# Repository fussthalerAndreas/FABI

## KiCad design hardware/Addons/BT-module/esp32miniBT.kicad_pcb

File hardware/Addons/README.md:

# FABI Hardware Addons

This folder contains any additional piece of software hardware or gadget to increase the usability of the FABI box.
Since we use a plain Arduino Pro Micro, these addons are fitted on the corresponding and available pin headers.

## BT-module

The BT module is an ESP32 based addon board for the FABI box. It is placed via pin headers (please do not solder directly, as it is likely that the USB port will break some day) on the supply & serial pins.
This folder here contains the KiCAD design files for PCB production.
Please refer to [esp32_mouse_keyboard](https://github.com/asterics/esp32_mouse_keyboard) repository for the corresponding source code.

This design was done in KiCAD __v5.1.6__. Please use a version equal or newer.

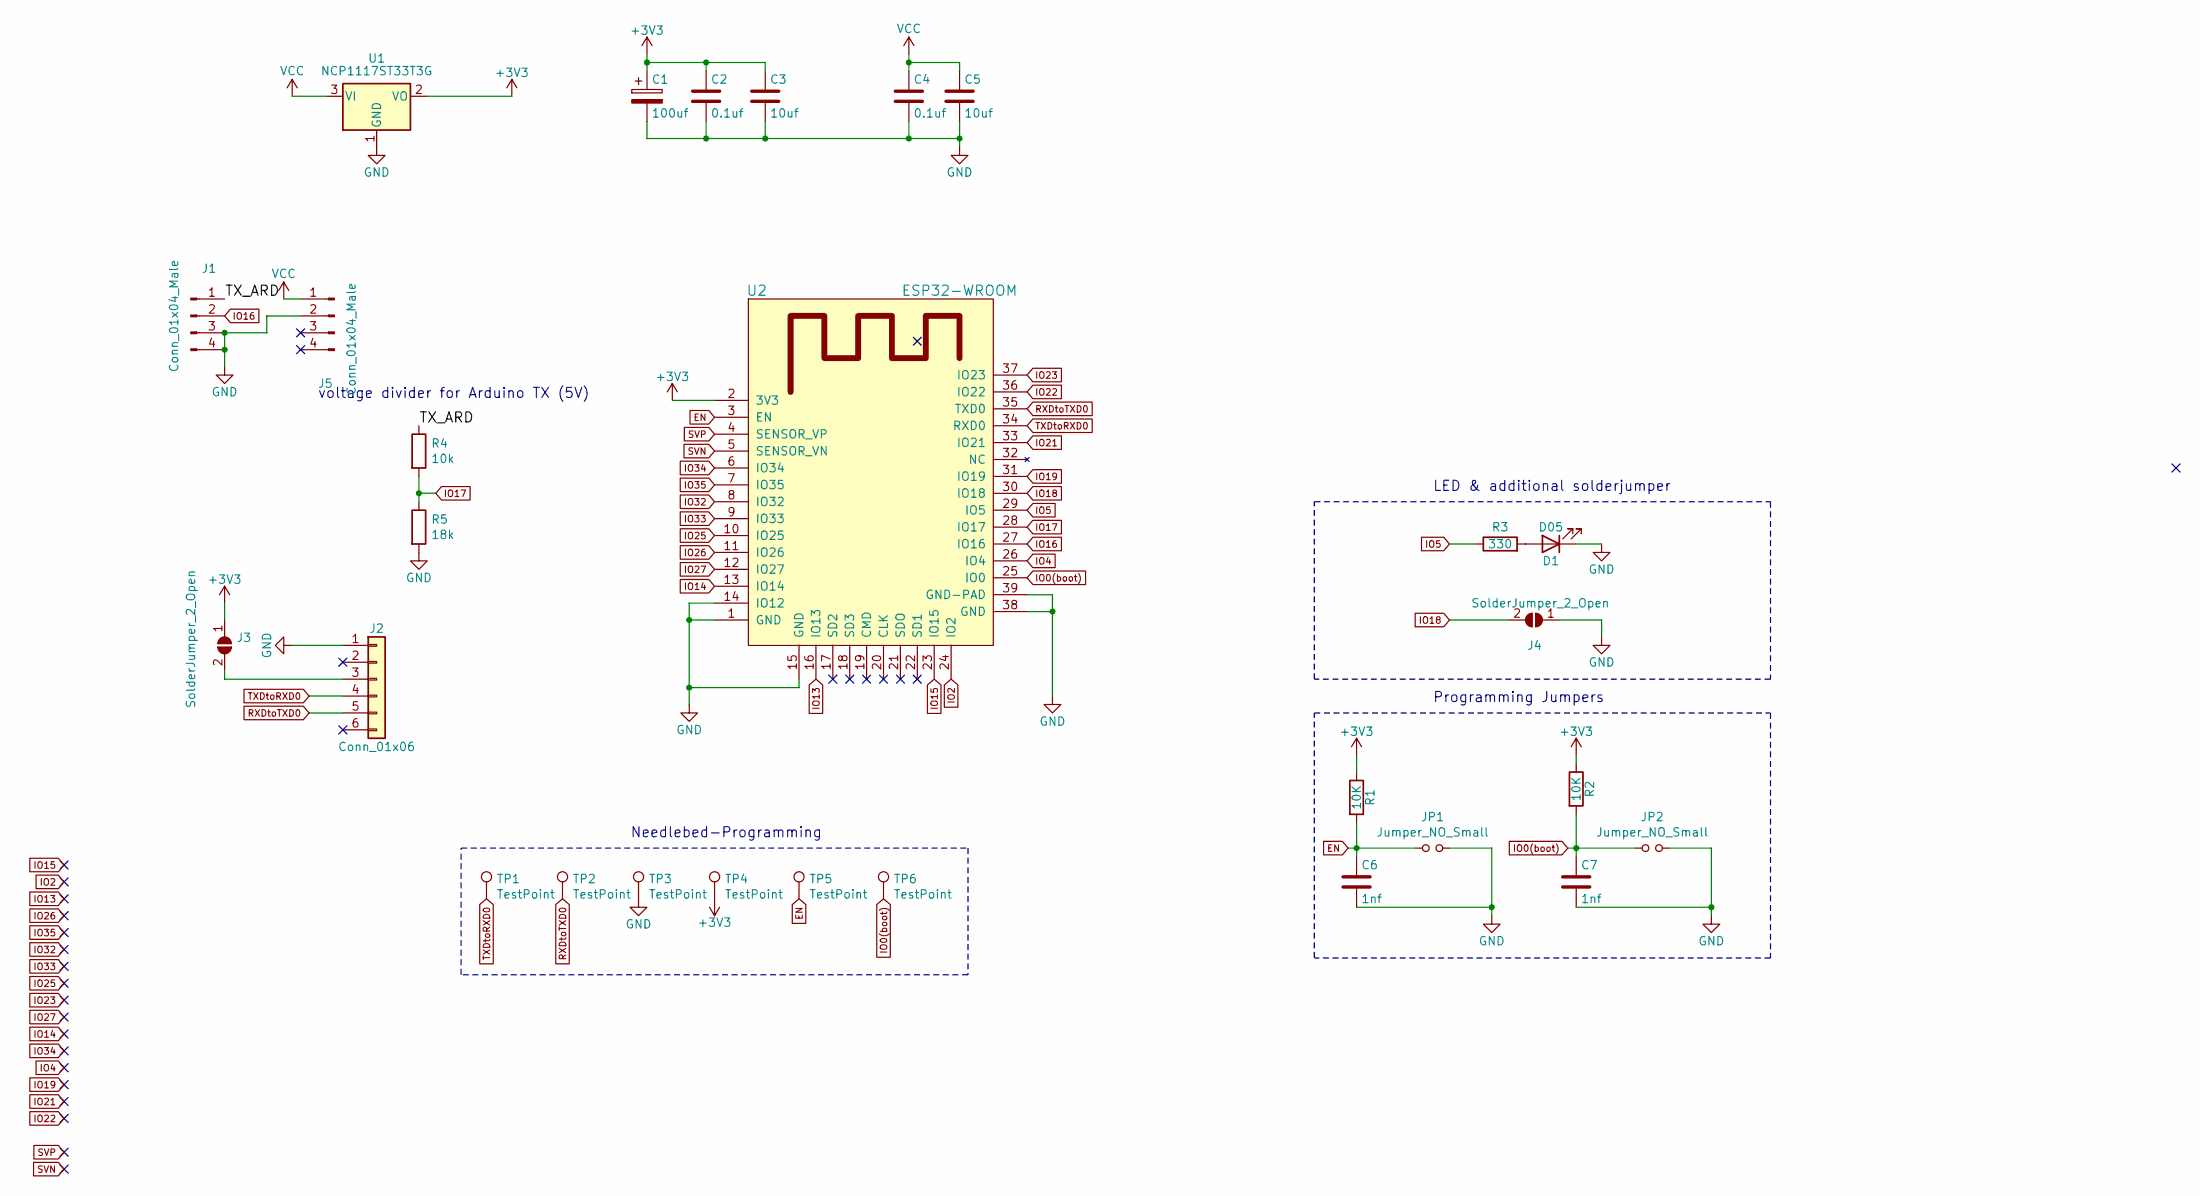
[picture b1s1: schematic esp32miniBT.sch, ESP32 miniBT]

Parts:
C1: 100uf; C_1206_3216Metric_Pad1.42x1.75mm_HandSolder
C2, C4: 0.1uf; C_0603_1608Metric_Pad1.05x0.95mm_HandSolder
C3, C5: 10uf; C_0603_1608Metric_Pad1.05x0.95mm_HandSolder
C6, C7: 1nf; C_0603_1608Metric_Pad1.05x0.95mm_HandSolder
D1: D05; LED_D3.0mm
J1, J5: Conn_01x04_Male; PinHeader_1x04_P2.54mm_Vertical_SMD_Pin1Left
J2: Conn_01x06; PinHeader_1x06_P2.54mm_Horizontal
J3, J4: SolderJumper_2_Open; SolderJumper-2_P1.3mm_Open_Pad1.0x1.5mm
JP1, JP2: Jumper_NO_Small; PinHeader_1x02_P2.54mm_Vertical
R1, R2: 10K; R_0603_1608Metric_Pad1.05x0.95mm_HandSolder
R3: 330; R_0603_1608Metric_Pad1.05x0.95mm_HandSolder
R4: 10k; R_0603_1608Metric_Pad1.05x0.95mm_HandSolder
R5: 18k; R_0603_1608Metric_Pad1.05x0.95mm_HandSolder
TP1, TP2, TP3, TP4, TP5, TP6: TestPoint; TestPoint_Pad_1.0x1.0mm
U1: NCP1117ST33T3G; SOT-223-3_TabPin2
U2: ESP32-WROOM

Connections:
+3V3: C1.1, C2.1, C3.1, J3.1 (A), R1.1, R2.1, TP4.1, U1.2 (VO), U2.2 (3V3)
/TX_ARD: J1.1, R4.1
EN: C6.1, JP1.1, R1.2, TP5.1, U2.3 (EN)
GND: C1.2, C2.2, C3.2, C4.2, C5.2, C6.2, C7.2, D1.1 (K), J1.3, J1.4, J2.1, J4.1 (A), J5.2, JP1.2, JP2.2, R5.2, TP3.1, U1.1 (GND), U2.1 (GND), U2.14 (IO12), U2.15 (GND), U2.38 (GND), U2.39 (GND-PAD)
IO0(boot): C7.1, JP2.1, R2.2, TP6.1, U2.25 (IO0)
IO2: U2.24 (IO2)
IO4: U2.26 (IO4)
IO5: R3.1, U2.29 (IO5)
IO13: U2.16 (IO13)
IO14: U2.13 (IO14)
IO15: U2.23 (IO15)
IO16: J1.2, U2.27 (IO16)
IO17: R4.2, R5.1, U2.28 (IO17)
IO18: J4.2 (B), U2.30 (IO18)
IO19: U2.31 (IO19)
IO21: U2.33 (IO21)
IO22: U2.36 (IO22)
IO23: U2.37 (IO23)
IO25: U2.10 (IO25)
IO26: U2.11 (IO26)
IO27: U2.12 (IO27)
IO32: U2.8 (IO32)
IO33: U2.9 (IO33)
IO34: U2.6 (IO34)
IO35: U2.7 (IO35)
unnamed: D1.2 (A), R3.2
unnamed: J2.3, J3.2 (B)
RXDtoTXD0: J2.5, TP2.1, U2.35 (TXD0)
SVN: U2.5 (SENSOR_VN)
SVP: U2.4 (SENSOR_VP)
TXDtoRXD0: J2.4, TP1.1, U2.34 (RXD0)
VCC: C4.1, C5.1, J5.1, U1.3 (VI)

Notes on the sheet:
Programming Jumpers
LED & additional solderjumper
Needlebed-Programming
voltage divider for Arduino TX (5V)

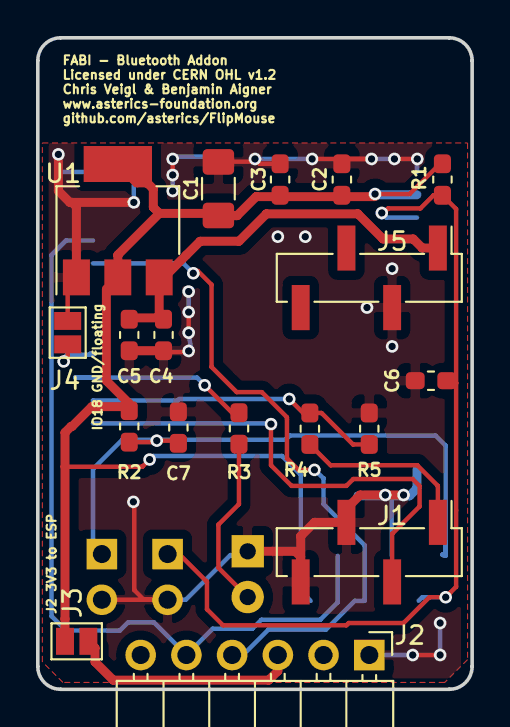
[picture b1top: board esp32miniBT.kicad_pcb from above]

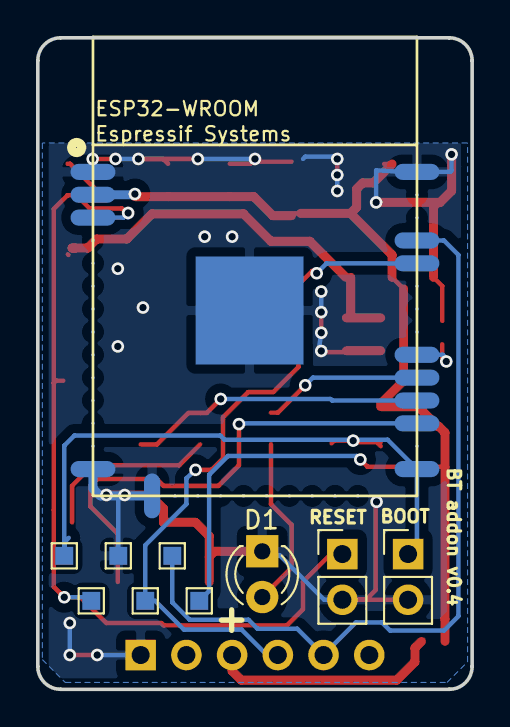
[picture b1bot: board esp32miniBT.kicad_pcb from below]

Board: 2 copper layers, 24.1 x 36.2 mm, 28 parts (10 on the bottom side), 14 nets.

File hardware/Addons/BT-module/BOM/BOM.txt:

BOM for ESP32miniBT add-on module for FlipMouse
===============================================

U1:      Low-Dropout-Regulator 3,3V  (NCP1117ST33T)  Farnell 1825376
U2:      Espressif             ESP32 (Wroom PCB)     Mouser: 356-ESP-WROOM-32  (or via ebay, aliexpress etc.)
C1:      Capacitor             100uf (1206)          Farnell: 2852775
C2,C4:   Capacitor             100nf (0603)          Farnell: 1327731
C3,C5:   Capacitor              10uf (0603)          Farnell: 2346889
C6,C7:   Capacitor               1nf (0603)          Farnell: 2280655
R1,R2:   Resistor                10k (0603)          Farnell: 2140192
R3:      Resistor               330R (0603)          Farnell: 2502447
D1:      LED SMD               green (0603)          Farnell: 2687486
J1,J5:	 01x04 SMD pin header						 Farnell: 2847169

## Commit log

2017-10-23 Added Logo, added programmer pogo pin case
2017-11-02 First draft of new keyboard layouts, first BT HM10 draft
2020-08-13 Added Bluetooth/USB HID abstraction layer from FLipMouse
2020-08-13 Added Bluetooth addon board, compatible with Arduino ProMicro
2021-04-28 updated Case Display cut, due to different display length of AZ-Delivery
2021-04-29 FABI Case *) Bottom: repositioned USB light cut *) Top: adjusted Display cut for AZ-Delivery and bigger displays
2021-05-25 added FABI mini case

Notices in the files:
hardware/Addons/BT-module/esp32miniBT.kicad_pcb:
Licensed under CERN OHL v1.2
